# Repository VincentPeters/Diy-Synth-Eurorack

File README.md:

# Diy Synth Eurorack

Collection of files about diy synth making, mostly eurorack format.

This is more of a personal archive. I don't own most of these assets. 

If you want something removed, please contact me.

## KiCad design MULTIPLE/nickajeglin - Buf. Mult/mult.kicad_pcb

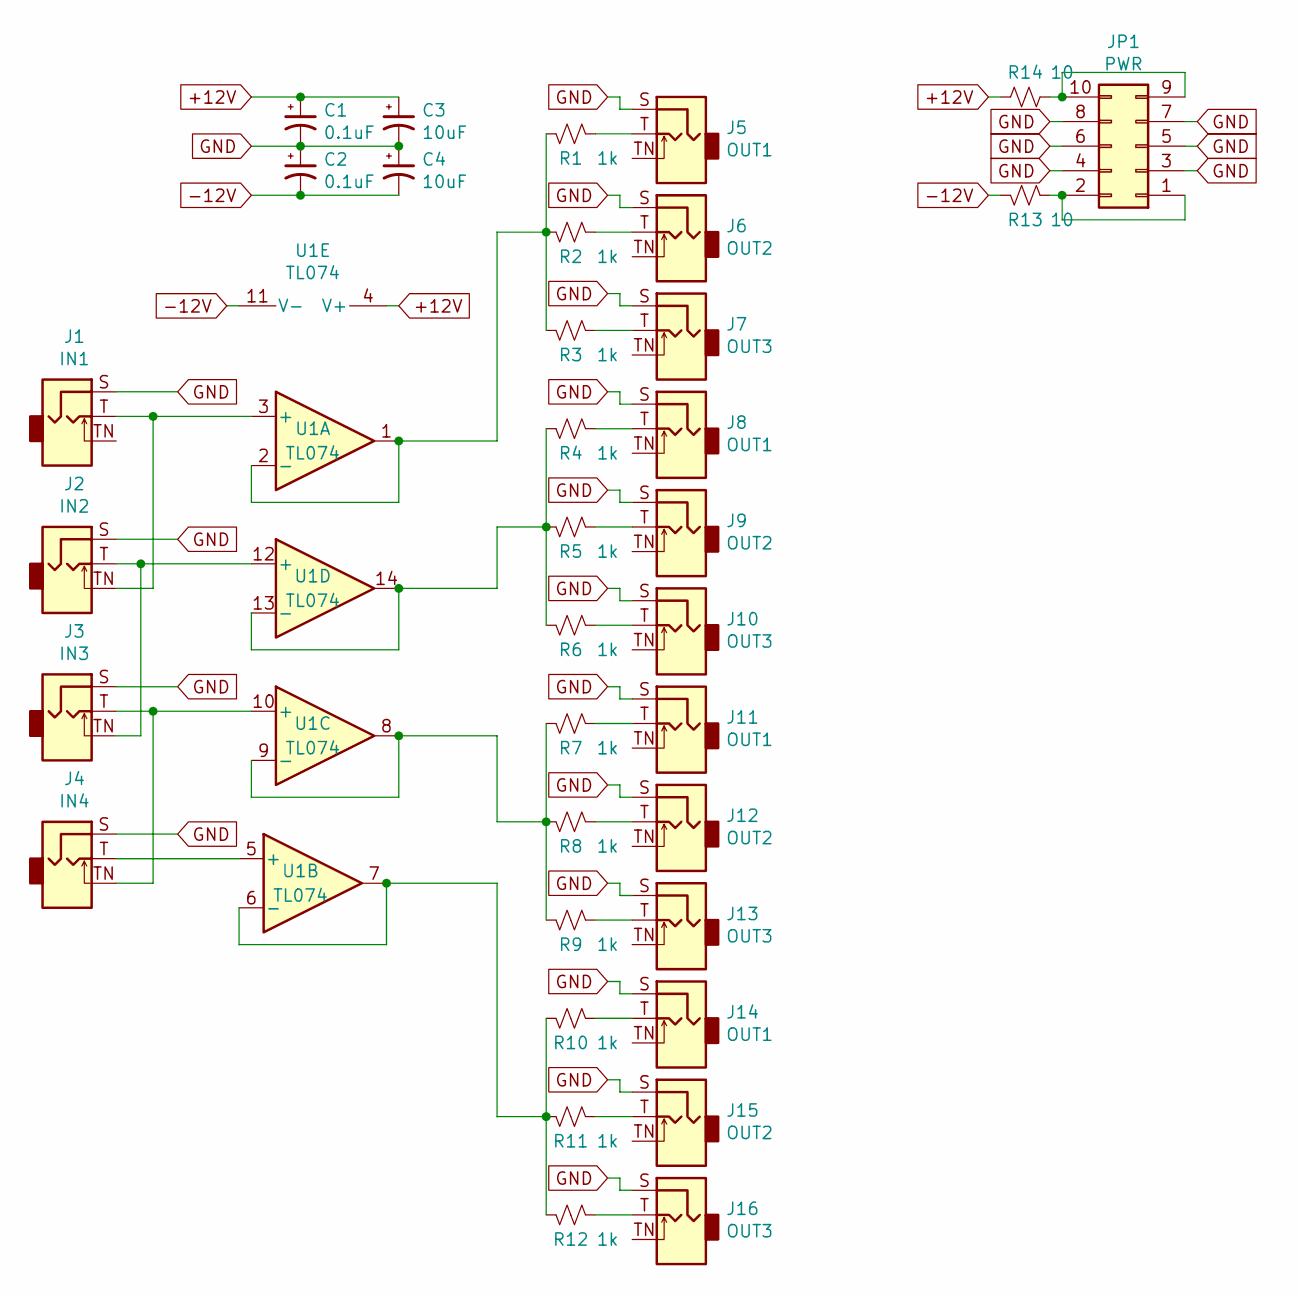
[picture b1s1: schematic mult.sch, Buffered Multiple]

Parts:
C1, C2: 0.1uF; C_Disc_D3.0mm_W1.6mm_P2.50mm
C3, C4: 10uF; CP_Radial_D5.0mm_P2.50mm
J1: IN1; 3.5mm_tip_switch_thonkiconn
J2: IN2; 3.5mm_tip_switch_thonkiconn
J3: IN3; 3.5mm_tip_switch_thonkiconn
J4: IN4; 3.5mm_tip_switch_thonkiconn
J5, J8, J11, J14: OUT1; 3.5mm_tip_switch_thonkiconn
J6, J9, J12, J15: OUT2; 3.5mm_tip_switch_thonkiconn
J7, J10, J13, J16: OUT3; 3.5mm_tip_switch_thonkiconn
JP1: PWR; IDC-Header_2x05_P2.54mm_Vertical
R1, R2, R3, R4, R5, R6, R7, R8, R9, R10, R11, R12: 1k; R_Axial_DIN0207_L6.3mm_D2.5mm_P7.62mm_Horizontal
R13, R14: 10; R_Axial_DIN0207_L6.3mm_D2.5mm_P7.62mm_Horizontal
U1: TL074; DIP-14_W7.62mm

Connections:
+12V: C1.1, C3.1, R14.2, U1.4 (V+)
-12V: C2.2, C4.2, R13.2, U1.11 (V-)
GND: C1.2, C2.1, C3.2, C4.1, J1.S, J2.S, J3.S, J4.S, J5.S, J6.S, J7.S, J8.S, J9.S, J10.S, J11.S, J12.S, J13.S, J14.S, J15.S, J16.S, JP1.3, JP1.4, JP1.5, JP1.6, JP1.7, JP1.8
unnamed: J1.T, J2.TN, U1.3 (+)
unnamed: J2.T, J3.TN, U1.12 (+)
unnamed: J3.T, J4.TN, U1.10 (+)
unnamed: J4.T, U1.5 (+)
unnamed: J5.T, R1.1
unnamed: J6.T, R2.1
unnamed: J7.T, R3.1
unnamed: J8.T, R4.1
unnamed: J9.T, R5.1
unnamed: J10.T, R6.1
unnamed: J11.T, R7.1
unnamed: J12.T, R8.1
unnamed: J13.T, R9.1
unnamed: J14.T, R10.1
unnamed: J15.T, R11.1
unnamed: J16.T, R12.1
unnamed: JP1.1, JP1.2, R13.1
unnamed: JP1.9, JP1.10, R14.1
unnamed: R1.2, R2.2, R3.2, U1.1, U1.2 (-)
unnamed: R4.2, R5.2, R6.2, U1.13 (-), U1.14
unnamed: R7.2, R8.2, R9.2, U1.8, U1.9 (-)
unnamed: R10.2, R11.2, R12.2, U1.6 (-), U1.7

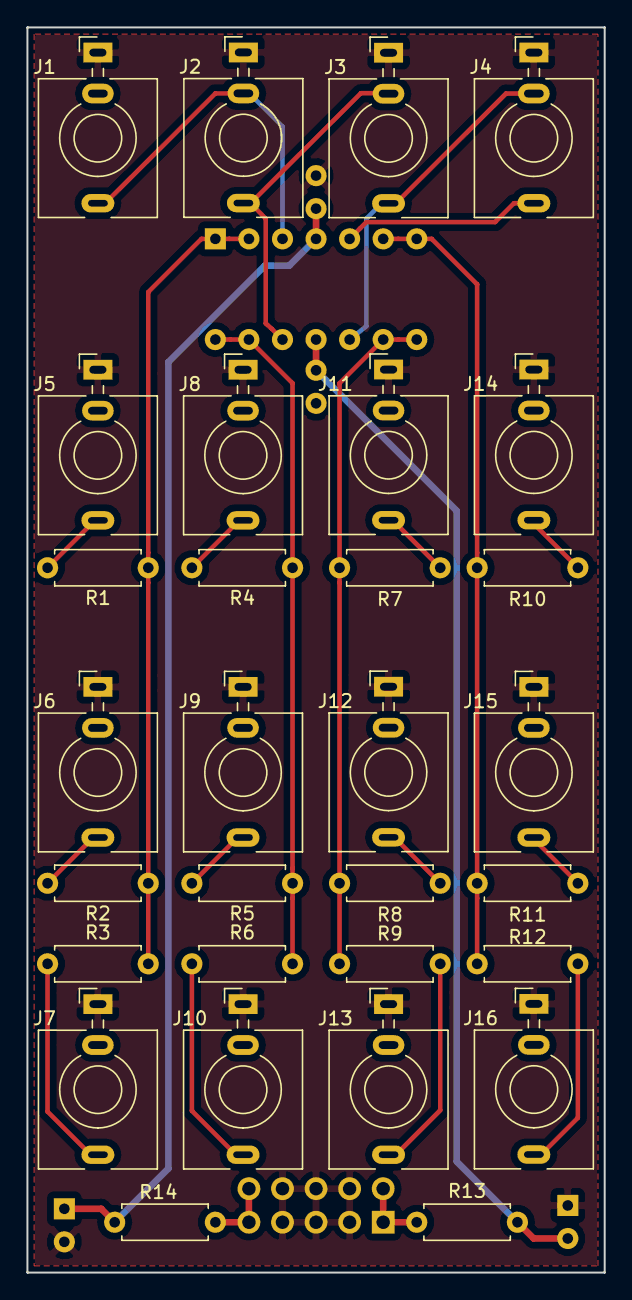
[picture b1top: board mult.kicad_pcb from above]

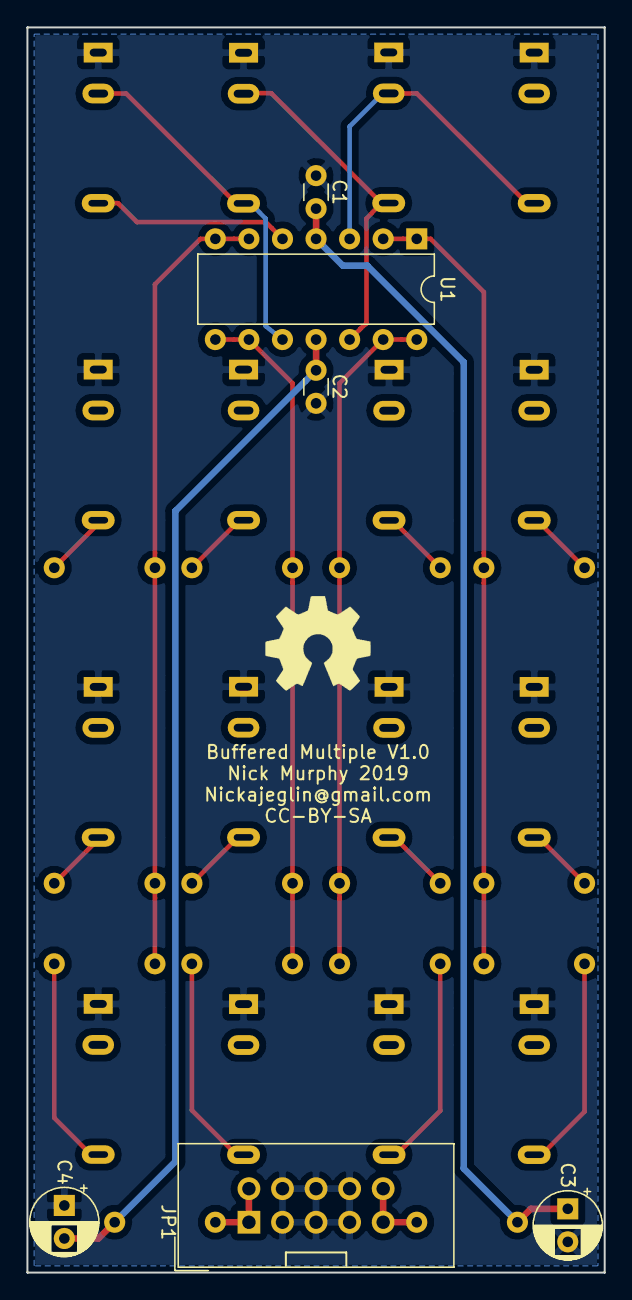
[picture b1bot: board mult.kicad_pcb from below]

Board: 2 copper layers, 43.7 x 94.2 mm, 36 parts (6 on the bottom side), 25 nets.

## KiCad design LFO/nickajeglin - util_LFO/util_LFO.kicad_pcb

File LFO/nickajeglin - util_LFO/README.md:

# source

https://github.com/nickajeglin/Eurorack-pcbs

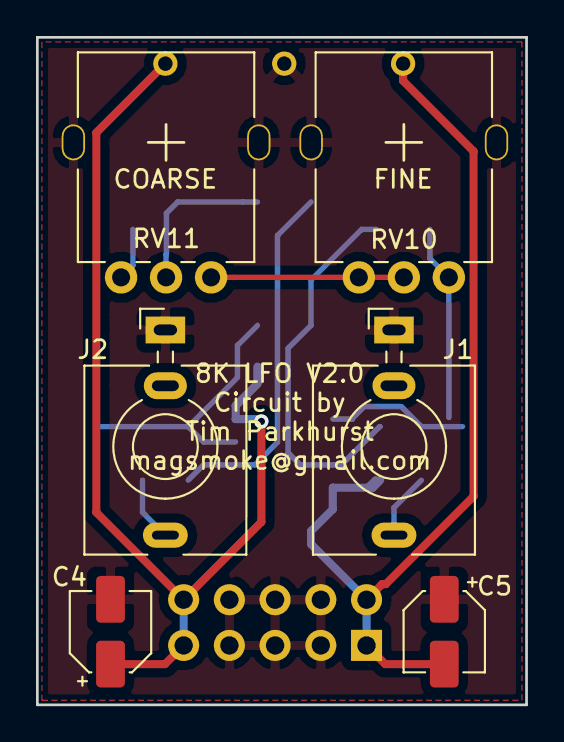
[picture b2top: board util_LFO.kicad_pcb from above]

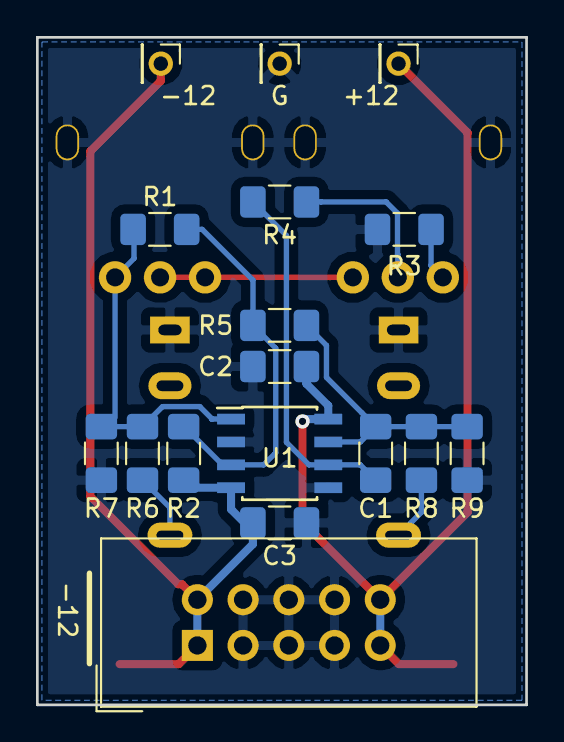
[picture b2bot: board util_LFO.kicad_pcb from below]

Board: 2 copper layers, 27.2 x 37.1 mm, 23 parts (17 on the bottom side), 12 nets.

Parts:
C1: 3300pF; C_1206_3216Metric_Pad1.42x1.75mm_HandSolder
C2, C3: 0.1uF; C_1206_3216Metric_Pad1.42x1.75mm_HandSolder
C4, C5: 10uF; CP_Elec_4x5.4
J1: SQR; 3.5mm_tip_switch_thonkiconn
J2: TRI; 3.5mm_tip_switch_thonkiconn
J3: Conn_02x05_Odd_Even; IDC-Header_2x05_P2.54mm_Vertical
J4: +12; PinHeader_1x01_P2.00mm_Vertical
J5: GND; PinHeader_1x01_P2.00mm_Vertical
J6: -12; PinHeader_1x01_P2.00mm_Vertical
R1: 200K; R_1206_3216Metric_Pad1.42x1.75mm_HandSolder
R2: 5M; R_1206_3216Metric_Pad1.42x1.75mm_HandSolder
R3: 220R; R_1206_3216Metric_Pad1.42x1.75mm_HandSolder
R4: 1M; R_1206_3216Metric_Pad1.42x1.75mm_HandSolder
R5: 100K; R_1206_3216Metric_Pad1.42x1.75mm_HandSolder
R6, R9: 10K; R_1206_3216Metric_Pad1.42x1.75mm_HandSolder
R7: 4.7K; R_1206_3216Metric_Pad1.42x1.75mm_HandSolder
R8: 2K; R_1206_3216Metric_Pad1.42x1.75mm_HandSolder
RV10, RV11: A1M; Potentiometer_Thonk_Alpha_9mm_Vertical
U1: TL072; SOIC-8_3.9x4.9mm_P1.27mm

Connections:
+12v: C2.1, C4.1, J3.9, J3.10, J4.1, U1.8
-12V: C3.2, C5.2, J3.1, J3.2, J6.1, R2.2, U1.4
GND: C2.2, C3.1, C4.2, C5.1, J1.S, J2.S, J3.3, J3.4, J3.5, J3.6, J3.7, J3.8, J5.1, R3.1, R7.2, R9.2, U1.2, U1.5
unnamed: C1.1, R4.1, U1.6
unnamed: C1.2, R5.1, R8.1, R9.1, U1.7
unnamed: J1.T, R6.2
unnamed: J2.T, R8.2
unnamed: R1.1, R6.1, R7.1, RV10.1, U1.1
unnamed: R1.2, R2.1, R5.2, U1.3
unnamed: R3.2, RV11.3
unnamed: R4.2, RV11.2
unnamed: RV10.2, RV10.3, RV11.1

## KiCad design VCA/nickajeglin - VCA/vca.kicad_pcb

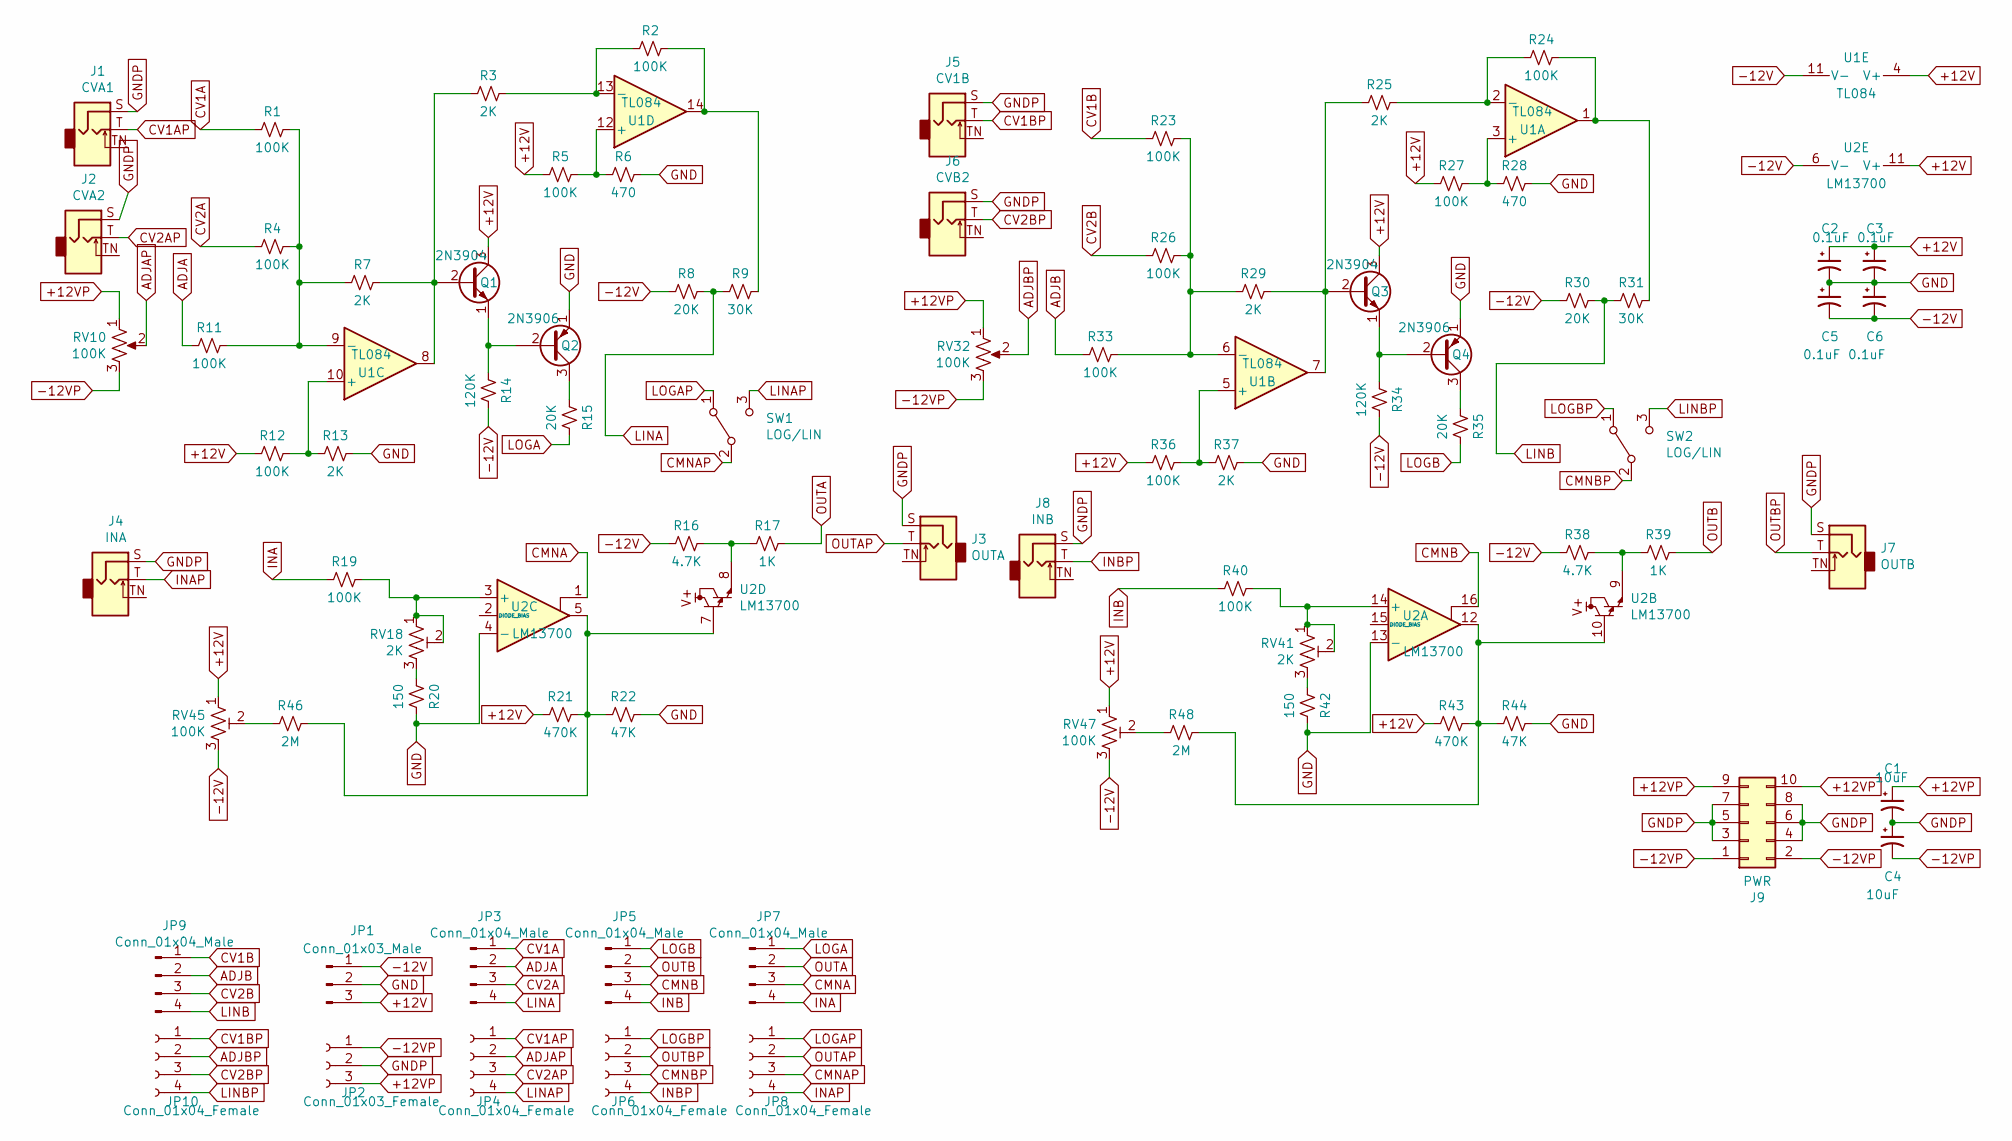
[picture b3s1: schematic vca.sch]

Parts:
C1, C4: 10uF; CP_Radial_D5.0mm_P2.50mm
C2, C3, C5, C6: 0.1uF; C_1206_3216Metric_Pad1.42x1.75mm_HandSolder
J1: CVA1; Jack_3.5mm_QingPu_WQP-PJ398SM_Vertical_CircularHoles
J2: CVA2; Jack_3.5mm_QingPu_WQP-PJ398SM_Vertical_CircularHoles
J3: OUTA; Jack_3.5mm_QingPu_WQP-PJ398SM_Vertical_CircularHoles
J4: INA; Jack_3.5mm_QingPu_WQP-PJ398SM_Vertical_CircularHoles
J5: CV1B; Jack_3.5mm_QingPu_WQP-PJ398SM_Vertical_CircularHoles
J6: CVB2; Jack_3.5mm_QingPu_WQP-PJ398SM_Vertical_CircularHoles
J7: OUTB; Jack_3.5mm_QingPu_WQP-PJ398SM_Vertical_CircularHoles
J8: INB; Jack_3.5mm_QingPu_WQP-PJ398SM_Vertical_CircularHoles
J9: PWR; IDC-Header_2x05_P2.54mm_Vertical
JP1: Conn_01x03_Male; PinHeader_1x03_P2.54mm_Vertical
JP2: Conn_01x03_Female; PinHeader_1x03_P2.54mm_Vertical
JP3, JP5, JP7, JP9: Conn_01x04_Male; PinHeader_1x04_P2.54mm_Vertical
JP4, JP6, JP8, JP10: Conn_01x04_Female; PinHeader_1x04_P2.54mm_Vertical
Q1, Q3: 2N3904; TO-92_Inline
Q2, Q4: 2N3906; TO-92_Inline
R1, R2, R4, R5, R11, R12, R19, R23, R24, R26, R27, R33, R36, R40: 100K; R_1206_3216Metric_Pad1.42x1.75mm_HandSolder
R3, R7, R13, R25, R29, R37: 2K; R_1206_3216Metric_Pad1.42x1.75mm_HandSolder
R6, R28: 470; R_1206_3216Metric_Pad1.42x1.75mm_HandSolder
R8, R15, R30, R35: 20K; R_1206_3216Metric_Pad1.42x1.75mm_HandSolder
R9, R31: 30K; R_1206_3216Metric_Pad1.42x1.75mm_HandSolder
R14, R34: 120K; R_1206_3216Metric_Pad1.42x1.75mm_HandSolder
R16, R38: 4.7K; R_1206_3216Metric_Pad1.42x1.75mm_HandSolder
R17, R39: 1K; R_1206_3216Metric_Pad1.42x1.75mm_HandSolder
R20, R42: 150; R_1206_3216Metric_Pad1.42x1.75mm_HandSolder
R21, R43: 470K; R_1206_3216Metric_Pad1.42x1.75mm_HandSolder
R22, R44: 47K; R_1206_3216Metric_Pad1.42x1.75mm_HandSolder
R46, R48: 2M; R_1206_3216Metric_Pad1.42x1.75mm_HandSolder
RV10, RV32: 100K; Potentiometer_Bourns_PTV09A-1_Single_Vertical
RV18, RV41: 2K; Potentiometer_Bourns_3266Y_Vertical
RV45, RV47: 100K; Potentiometer_Bourns_3266Y_Vertical
SW1, SW2: LOG/LIN; toggle_switch_mini
U1: TL084; SOIC-14_3.9x8.7mm_P1.27mm
U2: LM13700; SOIC-16_4.55x10.3mm_P1.27mm

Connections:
+12V: C2.1, C3.1, JP1.3, Q1.3 (C), Q3.3 (C), R5.2, R12.2, R21.2, R27.2, R36.2, R43.2, RV45.1, RV47.1, U1.4 (V+), U2.11 (V+)
+12VP: C1.1, J9.9, J9.10, JP2.3, RV10.1, RV32.1
-12V: C5.2, C6.2, JP1.1, R8.2, R14.1, R16.2, R30.2, R34.1, R38.2, RV45.3, RV47.3, U1.11 (V-), U2.6 (V-)
-12VP: C4.2, J9.1, J9.2, JP2.1, RV10.3, RV32.3
ADJA: JP3.2, R11.2
ADJAP: JP4.2, RV10.2
ADJB: JP9.2, R33.2
ADJBP: JP10.2, RV32.2
CMNA: JP7.3, U2.1
CMNAP: JP8.3, SW1.2 (B)
CMNB: JP5.3, U2.16
CMNBP: JP6.3, SW2.2 (B)
CV1A: JP3.1, R1.2
CV1AP: J1.T, JP4.1
CV1B: JP9.1, R23.2
CV1BP: J5.T, JP10.1
CV2A: JP3.3, R4.2
CV2AP: J2.T, JP4.3
CV2B: JP9.3, R26.2
CV2BP: J6.T, JP10.3
GND: C2.2, C3.2, C5.1, C6.1, JP1.2, Q2.1 (E), Q4.1 (E), R6.1, R13.1, R20.1, R22.1, R28.1, R37.1, R42.1, R44.1, U2.4 (-), U2.13 (-)
GNDP: C1.2, C4.1, J1.S, J2.S, J3.S, J4.S, J5.S, J6.S, J7.S, J8.S, J9.3, J9.4, J9.5, J9.6, J9.7, J9.8, JP2.2
INA: JP7.4, R19.2
INAP: J4.T, JP8.4
INB: JP5.4, R40.2
INBP: J8.T, JP6.4
LINA: JP3.4, R8.1, R9.2
LINAP: JP4.4, SW1.3 (C)
LINB: JP9.4, R30.1, R31.2
LINBP: JP10.4, SW2.3 (C)
LOGA: JP7.1, R15.1
LOGAP: JP8.1, SW1.1 (A)
LOGB: JP5.1, R35.1
LOGBP: JP6.1, SW2.1 (A)
unnamed: Q1.1 (E), Q2.2 (B), R14.2
unnamed: Q1.2 (B), R3.2, R7.1, U1.8
unnamed: Q2.3 (C), R15.2
unnamed: Q3.1 (E), Q4.2 (B), R34.2
unnamed: Q3.2 (B), R25.2, R29.1, U1.7
unnamed: Q4.3 (C), R35.2
unnamed: R1.1, R4.1, R7.2, R11.1, U1.9 (-)
unnamed: R2.1, R9.1, U1.14
unnamed: R2.2, R3.1, U1.13 (-)
unnamed: R5.1, R6.2, U1.12 (+)
unnamed: R12.1, R13.2, U1.10 (+)
unnamed: R16.1, R17.2, U2.8
unnamed: R19.1, RV18.1, RV18.2, U2.3 (+)
unnamed: R20.2, RV18.3
unnamed: R21.1, R22.2, R46.1, U2.5, U2.7
unnamed: R23.1, R26.1, R29.2, R33.1, U1.6 (-)
unnamed: R24.1, R31.1, U1.1
unnamed: R24.2, R25.1, U1.2 (-)
unnamed: R27.1, R28.2, U1.3 (+)
unnamed: R36.1, R37.2, U1.5 (+)
unnamed: R38.1, R39.2, U2.9
unnamed: R40.1, RV41.1, RV41.2, U2.14 (+)
unnamed: R42.2, RV41.3
unnamed: R43.1, R44.2, R48.1, U2.10, U2.12
unnamed: R46.2, RV45.2
unnamed: R48.2, RV47.2
OUTA: JP7.2, R17.1
OUTAP: J3.T, JP8.2
OUTB: JP5.2, R39.1
OUTBP: J7.T, JP6.2

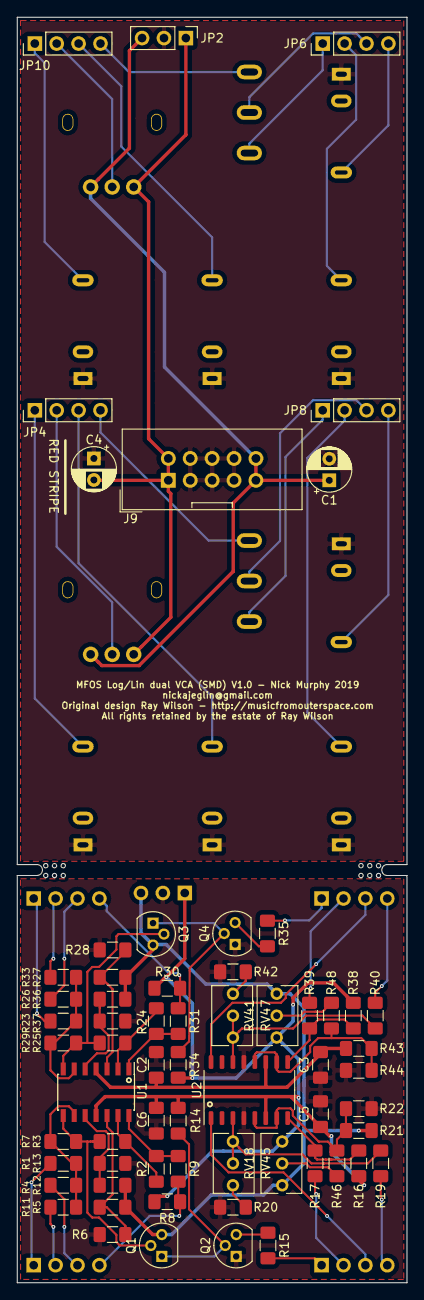
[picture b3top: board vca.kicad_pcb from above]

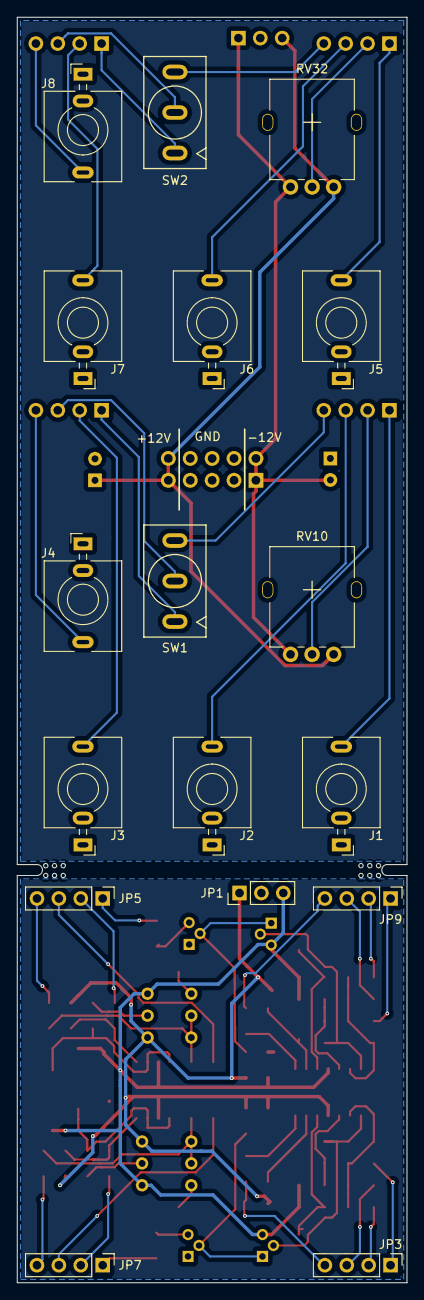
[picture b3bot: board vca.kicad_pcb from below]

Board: 2 copper layers, 45.2 x 146.8 mm, 81 parts (17 on the bottom side), 64 nets.

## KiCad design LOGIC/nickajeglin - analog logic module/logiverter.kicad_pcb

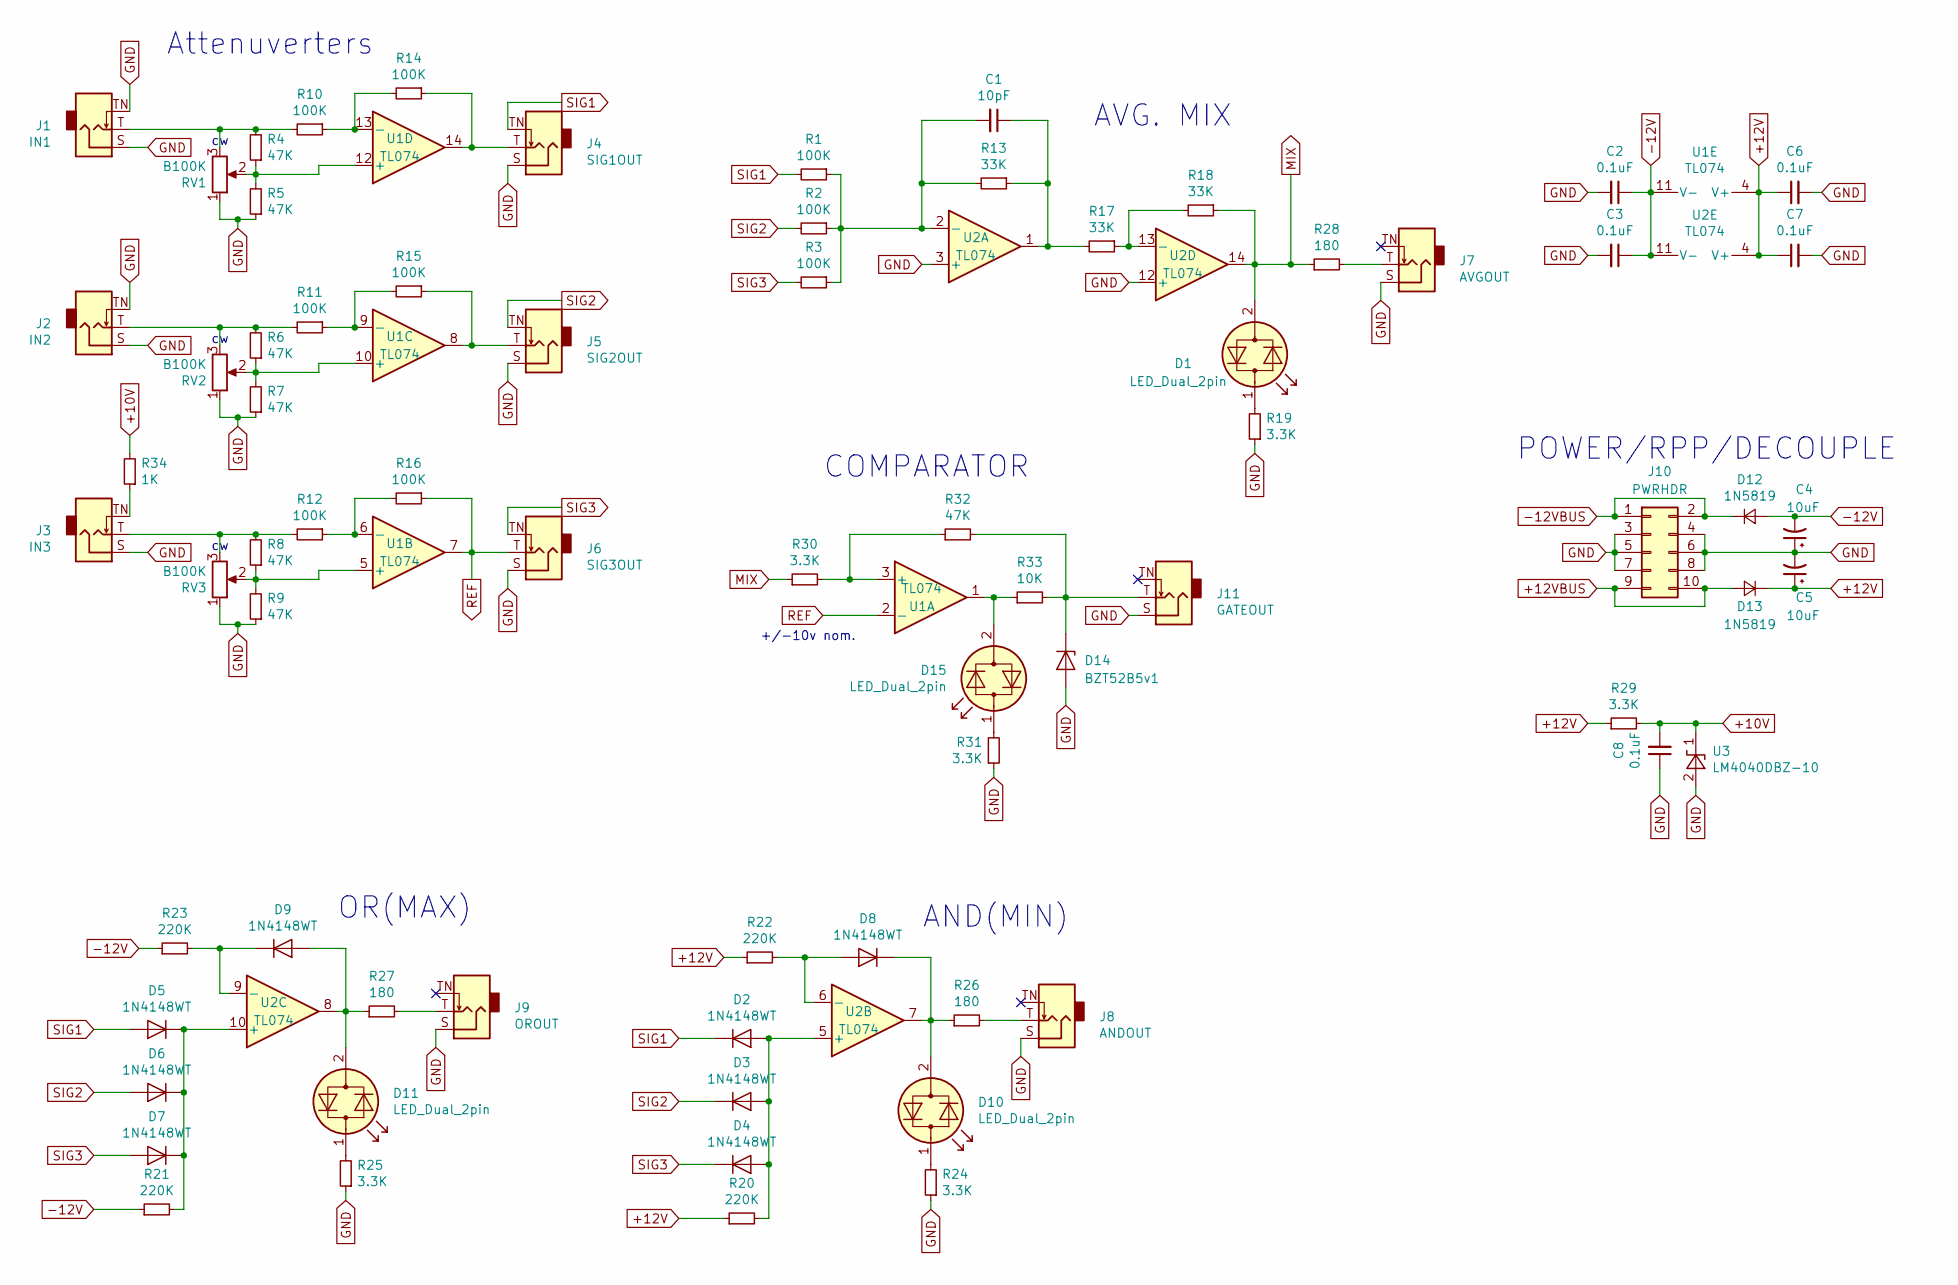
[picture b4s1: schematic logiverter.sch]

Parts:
C1: 10pF; C_0805_2012Metric_Pad1.15x1.40mm_HandSolder
C2, C3, C6, C7, C8: 0.1uF; C_0805_2012Metric_Pad1.15x1.40mm_HandSolder
C4, C5: 10uF; CP_Elec_5x5.4
D1, D10, D11, D15: LED_Dual_2pin; LED_D3.0mm
D2, D3, D4, D5, D6, D7, D8, D9: 1N4148WT; D_SOD-323_HandSoldering
D12, D13: 1N5819; D_SOD-123
D14: BZT52B5v1; D_SOD-123
J1: IN1; 3.5mm_tip_switch_thonkiconn
J2: IN2; 3.5mm_tip_switch_thonkiconn
J3: IN3; 3.5mm_tip_switch_thonkiconn
J4: SIG1OUT; 3.5mm_tip_switch_thonkiconn
J5: SIG2OUT; 3.5mm_tip_switch_thonkiconn
J6: SIG3OUT; 3.5mm_tip_switch_thonkiconn
J7: AVGOUT; 3.5mm_tip_switch_thonkiconn
J8: ANDOUT; 3.5mm_tip_switch_thonkiconn
J9: OROUT; 3.5mm_tip_switch_thonkiconn
J10: PWRHDR; IDC-Header_2x05_P2.54mm_Vertical
J11: GATEOUT; 3.5mm_tip_switch_thonkiconn
R1, R2, R3, R10, R11, R12, R14, R15, R16: 100K; R_0805_2012Metric_Pad1.15x1.40mm_HandSolder
R4, R5, R6, R7, R8, R9, R32: 47K; R_0805_2012Metric_Pad1.15x1.40mm_HandSolder
R13, R17, R18: 33K; R_0805_2012Metric_Pad1.15x1.40mm_HandSolder
R19, R24, R25, R29, R30, R31: 3.3K; R_0805_2012Metric_Pad1.15x1.40mm_HandSolder
R20, R21, R22, R23: 220K; R_0805_2012Metric_Pad1.15x1.40mm_HandSolder
R26, R27, R28: 180; R_0805_2012Metric_Pad1.15x1.40mm_HandSolder
R33: 10K; R_0805_2012Metric_Pad1.15x1.40mm_HandSolder
R34: 1K; R_0805_2012Metric_Pad1.15x1.40mm_HandSolder
RV1, RV2, RV3: B100K; Potentiometer_Vertical_Bournes_PTV09A
U1, U2: TL074; SOIC-14_3.9x8.7mm_P1.27mm
U3: LM4040DBZ-10; SOT-23_Handsoldering

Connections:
+10V: C8.2, R29.2, R34.2, U3.1 (K)
+12V: C5.1, C6.1, C7.1, D13.1 (K), R20.1, R22.1, R29.1, U1.4 (V+), U2.4 (V+)
+12VBUS: D13.2 (A), J10.9, J10.10
-12V: C2.1, C3.1, C4.2, D12.2 (A), R21.1, R23.1, U1.11 (V-), U2.11 (V-)
-12VBUS: D12.1 (K), J10.1, J10.2
GND: C2.2, C3.2, C4.1, C5.2, C6.2, C7.2, C8.1, D14.2 (A), J1.S, J1.TN, J2.S, J2.TN, J3.S, J4.S, J5.S, J6.S, J7.S, J8.S, J9.S, J10.3, J10.4, J10.5, J10.6, J10.7, J10.8, J11.S, R5.1, R7.1, R9.1, R19.1, R24.1, R25.1, R31.1, RV1.1, RV2.1, RV3.1, U2.3 (+), U2.12 (+), U3.2 (A)
MIX: D1.2 (AK), R18.1, R28.1, R30.1, U2.14
unnamed: C1.1, R13.1, R17.2, U2.1
unnamed: C1.2, R1.1, R2.1, R3.1, R13.2, U2.2 (-)
unnamed: D1.1 (KA), R19.2
unnamed: D2.2 (A), D3.2 (A), D4.2 (A), R20.2, U2.5 (+)
unnamed: D5.1 (K), D6.1 (K), D7.1 (K), R21.2, U2.10 (+)
unnamed: D8.2 (A), R22.2, U2.6 (-)
unnamed: D9.1 (K), R23.2, U2.9 (-)
unnamed: D10.1 (KA), R24.2
unnamed: D8.1 (K), D10.2 (AK), R26.1, U2.7
unnamed: D11.1 (KA), R25.2
unnamed: D9.2 (A), D11.2 (AK), R27.1, U2.8
unnamed: D14.1 (K), J11.T, R32.2, R33.2
unnamed: D15.1 (KA), R31.2
unnamed: D15.2 (AK), R33.1, U1.1
unnamed: J1.T, R4.2, R10.2, RV1.3
unnamed: J2.T, R6.2, R11.2, RV2.3
unnamed: J3.T, R8.2, R12.2, RV3.3
unnamed: J3.TN, R34.1
unnamed: J4.T, R14.1, U1.14
unnamed: J5.T, R15.1, U1.8
unnamed: J7.T, R28.2
unnamed: J8.T, R26.2
unnamed: J9.T, R27.2
unnamed: R4.1, R5.2, RV1.2, U1.12 (+)
unnamed: R6.1, R7.2, RV2.2, U1.10 (+)
unnamed: R8.1, R9.2, RV3.2, U1.5 (+)
unnamed: R10.1, R14.2, U1.13 (-)
unnamed: R11.1, R15.2, U1.9 (-)
unnamed: R12.1, R16.2, U1.6 (-)
unnamed: R17.1, R18.2, U2.13 (-)
unnamed: R30.2, R32.1, U1.3 (+)
REF: J6.T, R16.1, U1.2 (-), U1.7
SIG1: D2.1 (K), D5.2 (A), J4.TN, R1.2
SIG2: D3.1 (K), D6.2 (A), J5.TN, R2.2
SIG3: D4.1 (K), D7.2 (A), J6.TN, R3.2

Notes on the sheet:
Attenuverters
OR(MAX)
AND(MIN)
AVG. MIX
POWER/RPP/DECOUPLE
COMPARATOR
+/-10v nom.

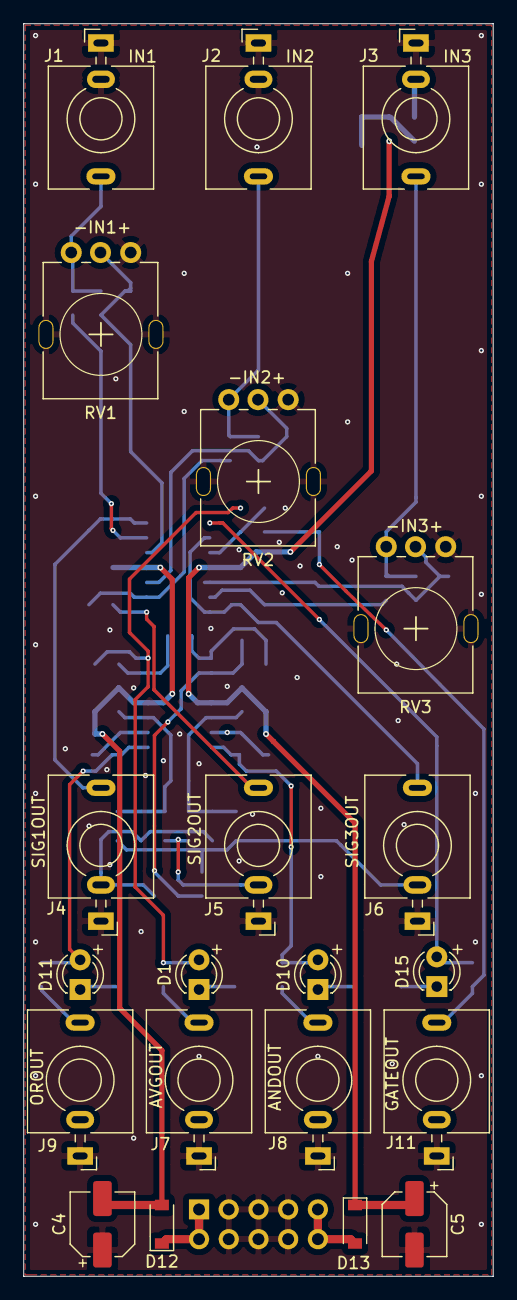
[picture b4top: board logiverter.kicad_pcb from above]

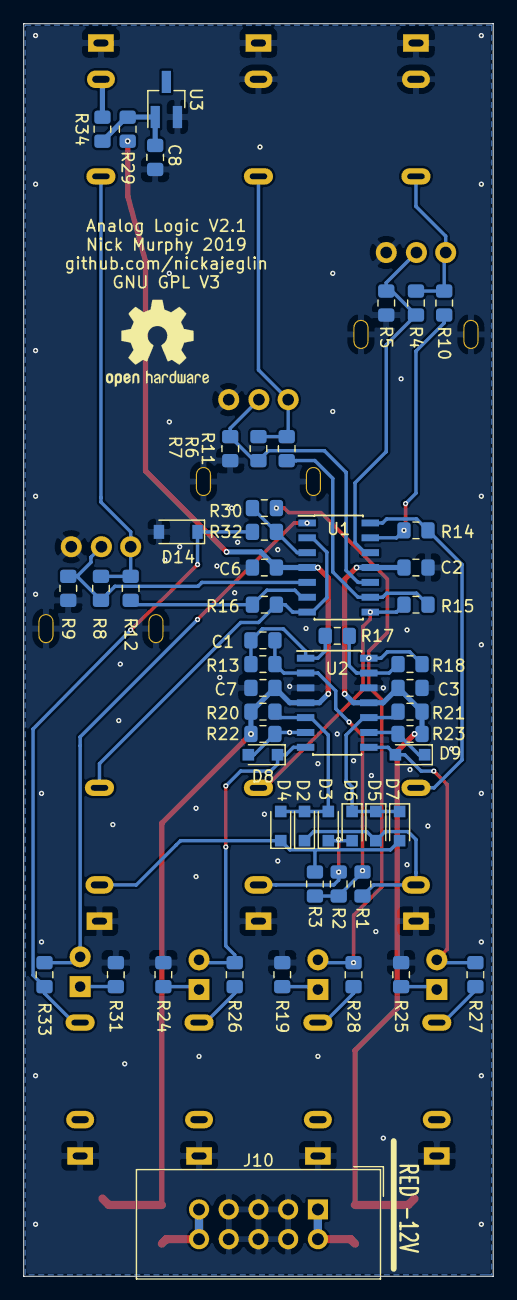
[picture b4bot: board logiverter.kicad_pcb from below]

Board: 2 copper layers, 40.1 x 107.1 mm, 74 parts (53 on the bottom side), 42 nets.

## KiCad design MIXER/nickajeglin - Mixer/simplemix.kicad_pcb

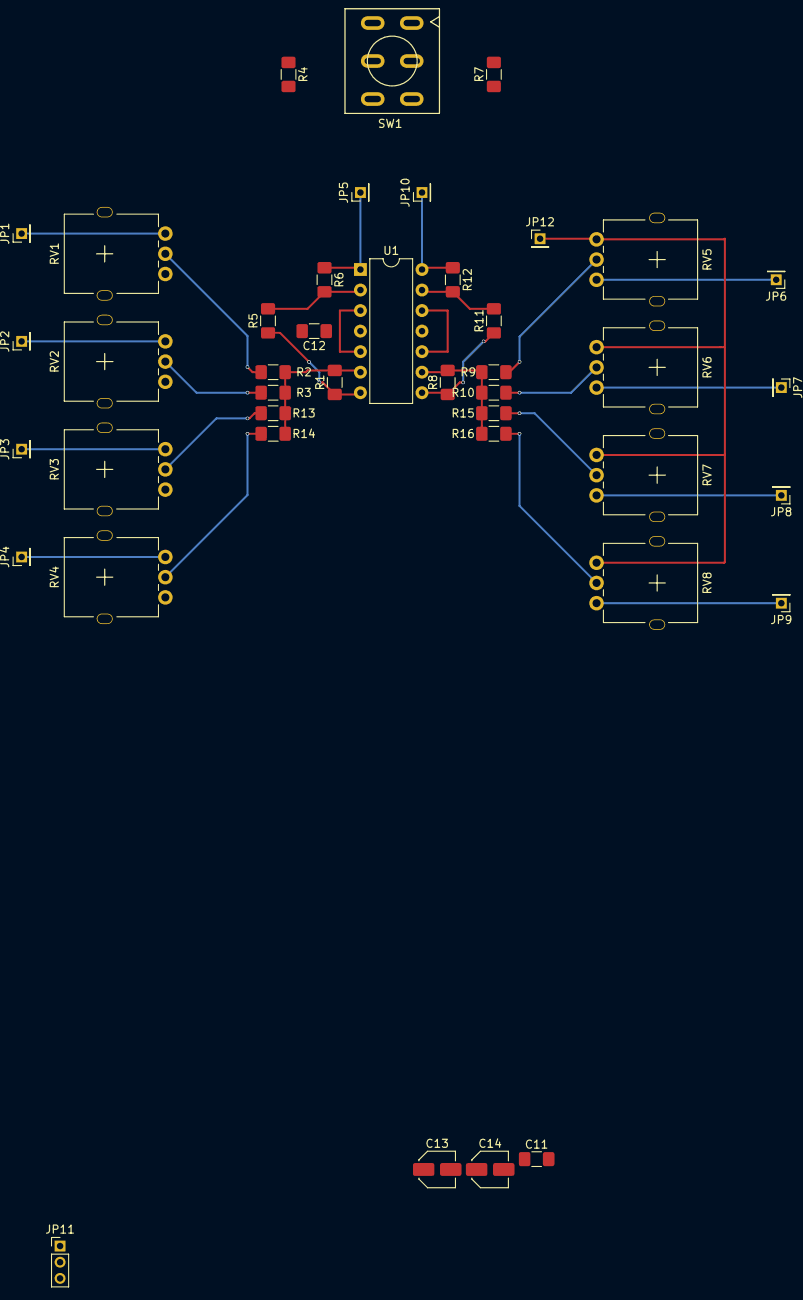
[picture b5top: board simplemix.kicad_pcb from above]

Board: 2 copper layers, 42 parts (0 on the bottom side), 29 nets.

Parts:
C11, C12: 0.1uF; C_1206_3216Metric_Pad1.42x1.75mm_HandSolder
C13, C14: 10uF; C_Elec_4x5.4
JP1: IN1; PinHeader_1x01_P2.00mm_Vertical
JP2: IN2; PinHeader_1x01_P2.00mm_Vertical
JP3: IN3; PinHeader_1x01_P2.00mm_Vertical
JP4: IN4; PinHeader_1x01_P2.00mm_Vertical
JP5: OUT1; PinHeader_1x01_P2.00mm_Vertical
JP6: IN5; PinHeader_1x01_P2.00mm_Vertical
JP7: IN6; PinHeader_1x01_P2.00mm_Vertical
JP8: IN7; PinHeader_1x01_P2.00mm_Vertical
JP9: IN8; PinHeader_1x01_P2.00mm_Vertical
JP10: OUT2; PinHeader_1x01_P2.00mm_Vertical
JP11: PWR CHAIN; PinHeader_1x03_P2.00mm_Vertical
JP12: GND; PinHeader_1x01_P2.00mm_Vertical
R1, R4, R5, R6, R7, R8, R11, R12: 100K; R_1206_3216Metric_Pad1.42x1.75mm_HandSolder
R2, R3, R9, R10, R13, R14, R15, R16: 33K; R_1206_3216Metric_Pad1.42x1.75mm_HandSolder
RV1, RV2, RV3, RV4, RV5, RV6, RV7, RV8: 100K; Potentiometer_Thonk_Alpha_9mm_Vertical
SW1: CONFIG; toggle_switch_mini_DPDT
U1: TL074; DIP-14_W7.62mm

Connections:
+12V: C12.1, C14.1, JP11.3, U1.4
-12V: C11.1, C13.2, JP11.1, U1.11
GND: C11.2, C12.2, C13.1, C14.2, JP11.2, JP12.1, RV1.3, RV2.3, RV3.3, RV4.3, RV5.3, RV6.3, RV7.3, RV8.3, U1.3, U1.5, U1.10, U1.12
unnamed: JP1.1, RV1.1
unnamed: JP2.1, RV2.1
unnamed: JP3.1, RV3.1
unnamed: JP4.1, RV4.1
unnamed: JP5.1, R6.1, U1.1
unnamed: JP6.1, RV5.1
unnamed: JP7.1, RV6.1
unnamed: JP8.1, RV7.1
unnamed: JP9.1, RV8.1
unnamed: JP10.1, R12.1, U1.14
unnamed: R1.1, R5.1, SW1.2, U1.7
unnamed: R1.2, R2.1, R3.1, R13.1, R14.1, U1.6
unnamed: R2.2, RV1.2
unnamed: R3.2, RV2.2
unnamed: R4.1, SW1.5
unnamed: R4.2, R5.2, R6.2, U1.2
unnamed: R7.2, SW1.1
unnamed: R9.2, RV5.2
unnamed: R8.2, R9.1, R10.1, R15.1, R16.1, U1.9
unnamed: R10.2, RV6.2
unnamed: R8.1, R11.1, SW1.4, U1.8
unnamed: R7.1, R11.2, R12.2, U1.13
unnamed: R13.2, RV3.2
unnamed: R14.2, RV4.2
unnamed: R15.2, RV7.2
unnamed: R16.2, RV8.2

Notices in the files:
LOGIC/nickajeglin - analog logic module/logiverter.kicad_pcb:
GNU GPL V3
MULTIPLE/nickajeglin - Buf. Mult/mult.kicad_pcb:
CC-BY-SA
VCO/Kassutronics - Avalanche VCO/source/AvalancheVCO.sch:
(C) 2018 Caspar Ockeloen-Korppi
